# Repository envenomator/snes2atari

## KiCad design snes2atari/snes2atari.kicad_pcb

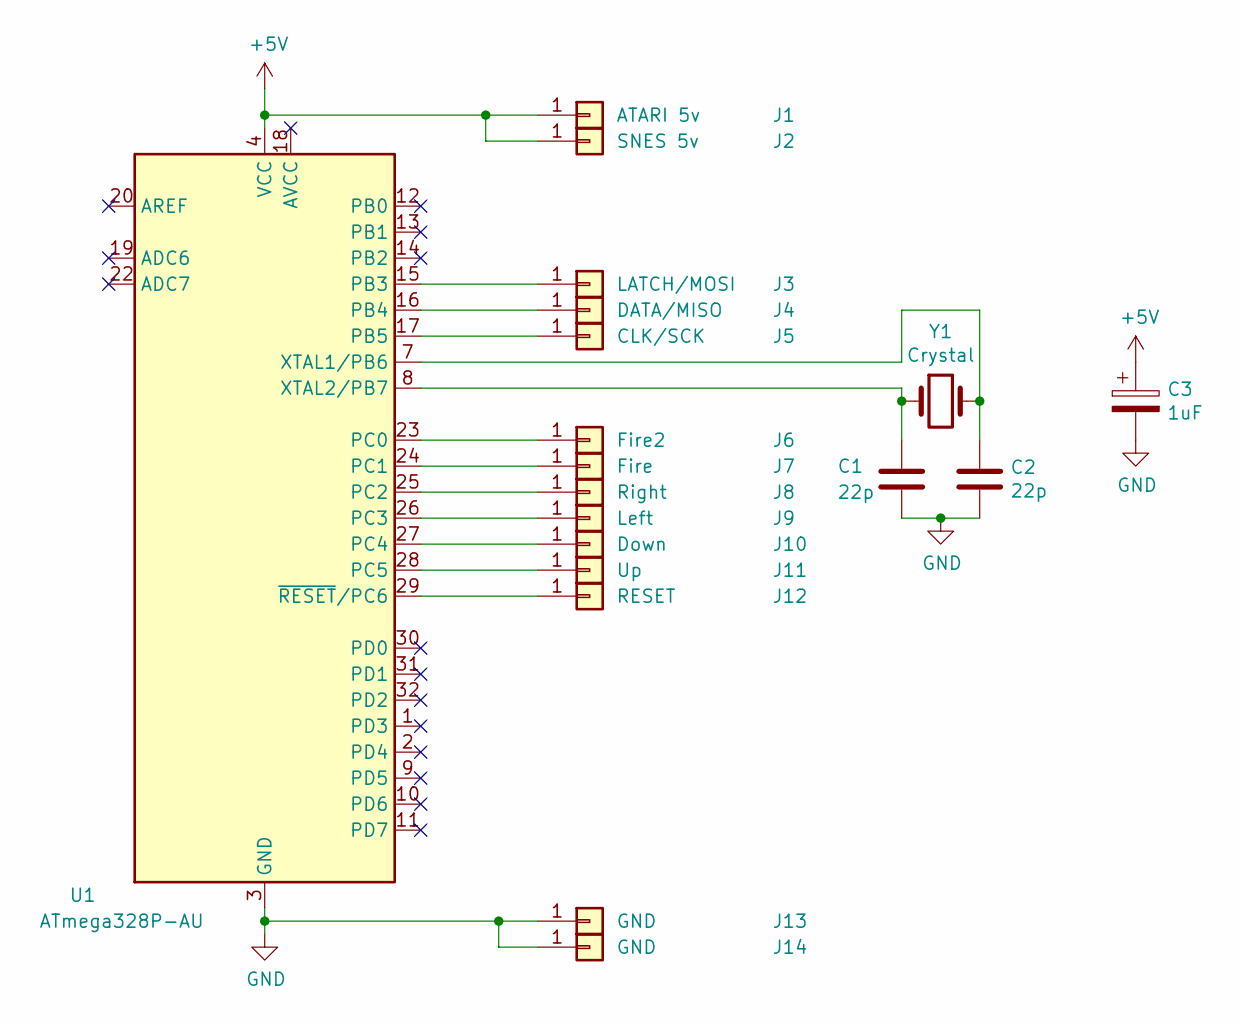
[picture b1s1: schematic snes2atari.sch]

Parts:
C1, C2: 22p; C_0805_2012Metric_Pad1.18x1.45mm_HandSolder
C3: 1uF; C_0805_2012Metric_Pad1.18x1.45mm_HandSolder
J1: ATARI 5v; SolderWire-0.25sqmm_1x01_D0.65mm_OD1.7mm
J2: SNES 5v; SolderWire-0.25sqmm_1x01_D0.65mm_OD1.7mm
J3: LATCH/MOSI; SolderWire-0.25sqmm_1x01_D0.65mm_OD1.7mm
J4: DATA/MISO; SolderWire-0.25sqmm_1x01_D0.65mm_OD1.7mm
J5: CLK/SCK; SolderWire-0.25sqmm_1x01_D0.65mm_OD1.7mm
J6: Fire2; SolderWire-0.25sqmm_1x01_D0.65mm_OD1.7mm
J7: Fire; SolderWire-0.25sqmm_1x01_D0.65mm_OD1.7mm
J8: Right; SolderWire-0.25sqmm_1x01_D0.65mm_OD1.7mm
J9: Left; SolderWire-0.25sqmm_1x01_D0.65mm_OD1.7mm
J10: Down; SolderWire-0.25sqmm_1x01_D0.65mm_OD1.7mm
J11: Up; SolderWire-0.25sqmm_1x01_D0.65mm_OD1.7mm
J12: RESET; SolderWire-0.25sqmm_1x01_D0.65mm_OD1.7mm
J13, J14: GND; SolderWire-0.25sqmm_1x01_D0.65mm_OD1.7mm
U1: ATmega328P-AU; TQFP-32_7x7mm_P0.8mm
Y1: Crystal; Crystal_HC49-U_Vertical

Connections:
+5V: C3.1, J1.1, J2.1, U1.4 (VCC), U1.6 (VCC)
GND: C1.2, C2.2, C3.2, J13.1, J14.1, U1.3 (GND), U1.5 (GND), U1.21 (GND)
unnamed: C1.1, U1.8 (XTAL2/PB7), Y1.1
unnamed: C2.1, U1.7 (XTAL1/PB6), Y1.2
unnamed: J3.1, U1.15 (PB3)
unnamed: J4.1, U1.16 (PB4)
unnamed: J5.1, U1.17 (PB5)
unnamed: J6.1, U1.23 (PC0)
unnamed: J7.1, U1.24 (PC1)
unnamed: J8.1, U1.25 (PC2)
unnamed: J9.1, U1.26 (PC3)
unnamed: J10.1, U1.27 (PC4)
unnamed: J11.1, U1.28 (PC5)
unnamed: J12.1, U1.29 (~RESET~/PC6)

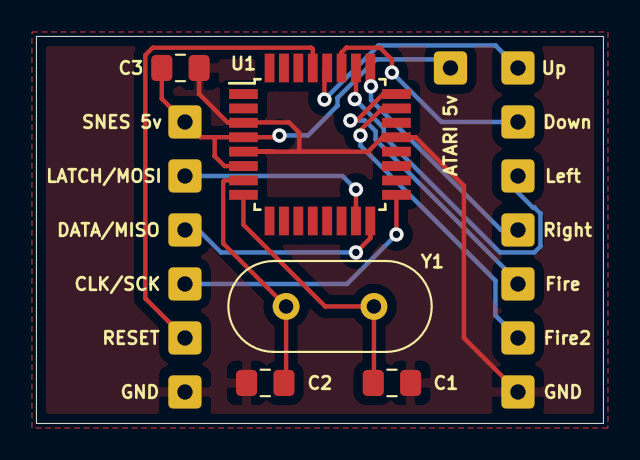
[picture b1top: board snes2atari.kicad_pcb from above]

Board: 2 copper layers, 31.5 x 21.5 mm, 19 parts (0 on the bottom side), 14 nets.

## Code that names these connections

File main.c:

/* Snes controller to Atari adapter
 * Copyright (C) 2013 Raphël Assénat
 * Adapted specifically for atari only with a single map
 *
 */
#include <stdint.h>
#include <string.h>
#include <avr/io.h>
#include <avr/interrupt.h>
#include <util/delay.h>

#include "snes.h"

#define OPT_AUTOFIRE			1		// This button is autofire
#define OPT_AUTOFIRE_SEL_SPEED	2		// This button cycles through autofire speeds
#define DB9_NULL				0x00
#define ATARI_BTN_DPAD_UP		0x20	// PC5
#define ATARI_BTN_DPAD_DOWN		0x10	// PC4
#define ATARI_BTN_DPAD_LEFT		0x08	// PC3
#define ATARI_BTN_DPAD_RIGHT	0x04	// PC2
#define ATARI_BTN_FIRE			0x02	// PC1
#define ATARI_BTN_FIRE2			0x01	// PC0
#define AUTOFIRE_SPEED_30		0 		// 60 / 2
#define AUTOFIRE_SPEED_25		1 		// 50 / 2
#define AUTOFIRE_SPEED_20		2 		// 60 / 3
#define AUTOFIRE_SPEED_16		3 		// 50 / 3
#define AUTOFIRE_SPEED_15		4 		// 60 / 4
#define AUTOFIRE_SPEED_12_5		5		// 50 / 4

struct snes_md_map {
	uint16_t snes_btn;
	uint8_t s; 
	char opts;
};

struct snes_md_map atari_style1_map[] = {
	{ SNES_BTN_DPAD_UP | SNES_BTN_A,		ATARI_BTN_DPAD_UP },
	{ SNES_BTN_DPAD_DOWN,					ATARI_BTN_DPAD_DOWN },
	{ SNES_BTN_DPAD_LEFT,					ATARI_BTN_DPAD_LEFT },
	{ SNES_BTN_DPAD_RIGHT,					ATARI_BTN_DPAD_RIGHT },
	{ SNES_BTN_B,							ATARI_BTN_FIRE },
	
	{ SNES_BTN_Y | SNES_BTN_R,				ATARI_BTN_FIRE,		OPT_AUTOFIRE },
	{ SNES_BTN_X | SNES_BTN_L,				ATARI_BTN_FIRE2, },
	{ SNES_BTN_SELECT,						DB9_NULL,			OPT_AUTOFIRE_SEL_SPEED },
	{ 0, }, /* SNES btns == 0 termination. */
};
// B is fire
// A is jump up, together with DPAD_UP
// Y/R provide rapidfire
// X/L provide fire2 for amiga
// START starts and stops autofire locking
// Menu cycles through autofire speeds

static uint8_t autofire_speed = AUTOFIRE_SPEED_25;
static uint8_t autofire_lock_on = 0;
static uint8_t autofire_state=0;

EMPTY_INTERRUPT(INT0_vect);

static void hwinit(void)
{
	/* PORTB
	 *
	 * Bit	Function	Dir		Level/pu
	 * 0	JP COM		out		0
	 * 1	JP1			in		1
	 * 2	JP2			in		1
	 * 3	SNES LATCH	out		0
	 * 4	SNES DAT	In		1
	 * 5	SNES CLK	out		1
	 * 6	XTAL1
	 * 7	XTAL2
	 */
	DDRB = 0x29;
	PORTB = 0x36;

	/* PORTC
	 *
	 * Bit	Function	Dir		Level/pull-up
	 * 0	START/C		In		1
	 * 1	A/B			In		1
	 * 2	0/RT/MODE	In		1
	 * 3	0/LF/X		In		1
	 * 4	DN/DN/Y		In		1
	 * 5	UP/UP/Z		In		1
	 */
	DDRC = 0x00;
	PORTC = 0xFF;

	/* PORTD
	 *
	 * Bit	Function	Dir		Level/pull-up
	 * 0	-			Out		0  \___ tied together on multiuse PCB2
	 * 1	-			Out		0  /
	 * 2	SELECT		In		1
	 * 3	-			Out		0
	 * 4	VCC			In		0  <---- Shorted to GND on multiuse PCB2
	 * 5	-			Out		0
	 * 6	-			Out		0
	 * 7	-			Out		0
	 */
	DDRD = 0xEB;
	PORTD = 0x04;

}

static void autofireCycleSpeed(uint8_t btn_state)
{
	static uint8_t last_state;

	if (btn_state && !last_state) {
		autofire_speed++;
		if (autofire_speed > AUTOFIRE_SPEED_12_5) {
			autofire_speed = AUTOFIRE_SPEED_30;
		}
	}

	last_state = btn_state;
}

static void autofireToggleLockOn(uint8_t btn_state)
{
	static uint8_t last_state;

	if (btn_state && !last_state) {
		autofire_lock_on = !autofire_lock_on;
	}

	last_state = btn_state;
}

static uint8_t autofireGetTop(void)
{
	switch (autofire_speed)
	{
			// divide by 2
		default:
		case AUTOFIRE_SPEED_30:
		case AUTOFIRE_SPEED_25:
			return 2;

			// divide by 3
		case AUTOFIRE_SPEED_20:
		case AUTOFIRE_SPEED_16:
			return 3;

			// divide by 4
		case AUTOFIRE_SPEED_15:
		case AUTOFIRE_SPEED_12_5:
			return 4;
	}
}

static void autofireSleep(void)
{
	switch (autofire_speed)
	{
			// 120Hz base
		default:
		case AUTOFIRE_SPEED_30:
		case AUTOFIRE_SPEED_20:
		case AUTOFIRE_SPEED_15:
//			_delay_us(8333);
			// This delay is trimmed to account for overhead and obtain 29.97Hz.
			_delay_us(8208);
			break;
	
			// 100Hz base
		case AUTOFIRE_SPEED_25:
		case AUTOFIRE_SPEED_16:
		case AUTOFIRE_SPEED_12_5:
			//_delay_us(10000); // 24.66
			_delay_us(9860); // 25 Hz
			break;
	}
}

static char autofirePoll(void)
{
	static uint8_t c=0;

	c = !c;

	return c;
}

static void autofireDo(void)
{
	static char autofire_count = 0;

	if (autofire_count <= 0) {
		autofire_count = autofireGetTop();
		autofire_state = !autofire_state;
	}
	autofire_count--;
}

int main(void)
{
	struct snes_md_map *map;
	gamepad_data last_data;
	uint8_t next_data = 0;
	Gamepad *snespad;

	hwinit();

	_delay_ms(20);

	snespad = snesGetGamepad();
	snespad->init(); 
	snespad->update();
	snespad->getReport(&last_data);


	while(1)
	{
		map = atari_style1_map;
		// Simulated open-collector/switch drive for Atari
		PORTC = 0x00;
		DDRC = next_data;

		autofireSleep();

		// make sure the controller is polled at
		// 50/60 hz regardless of the loop
		// timing for autofire which is higher.
		if (autofirePoll()) {
			snespad->update();
			snespad->getReport(&last_data);
		}

		autofireToggleLockOn(last_data.snes.buttons & SNES_BTN_START);
		autofireDo();

		next_data = 0;

		// walk through each button in the map structure
		while (map->snes_btn) {

			if (map->opts&OPT_AUTOFIRE) {
				if (autofire_lock_on) {
					if (autofire_state) {
						next_data |= map->s;
					}
				}
			}

			// any of the pressed buttons matches the mapping structure?
			if ((last_data.snes.buttons & map->snes_btn))
			{
				// set to commit, unless autofire
				if (!(map->opts&OPT_AUTOFIRE) || autofire_state) {
					next_data |= map->s;
				}
			}

			if ((map->opts&OPT_AUTOFIRE_SEL_SPEED)) {
				autofireCycleSpeed(last_data.snes.buttons & map->snes_btn);
			}

			map++;
		}
	
	}

	return 0;
}

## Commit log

2021-09-15 First code
2021-09-15 PCB complete
